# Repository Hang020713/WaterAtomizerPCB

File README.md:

# WaterAtomizerPCB
 A PCB Design of water atomizer

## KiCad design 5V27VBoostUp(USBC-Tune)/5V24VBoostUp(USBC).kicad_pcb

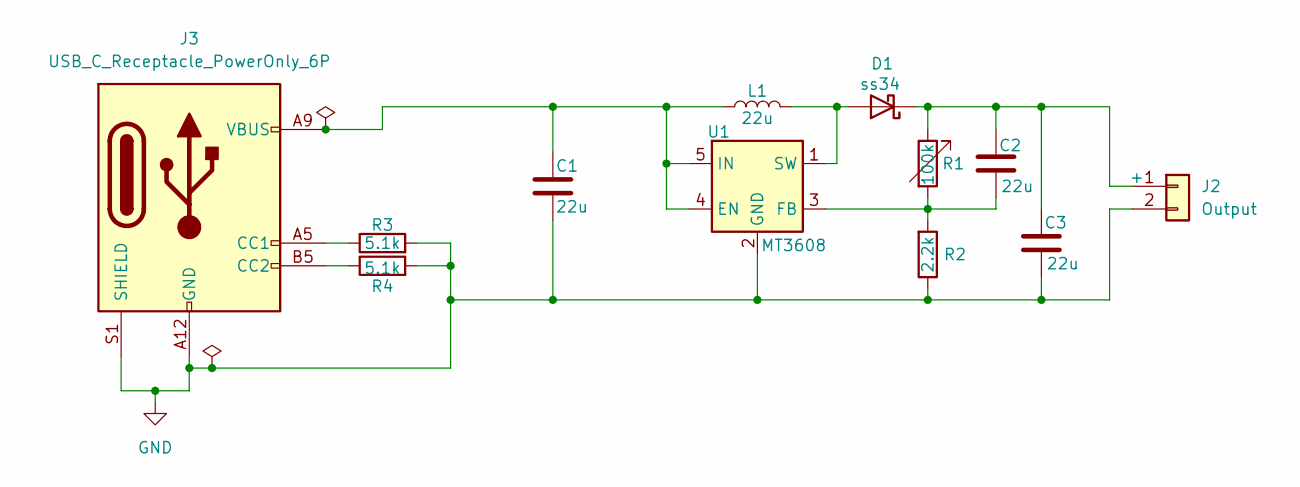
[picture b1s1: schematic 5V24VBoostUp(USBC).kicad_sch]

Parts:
C1, C2, C3: 22u; C_0603_1608Metric_Pad1.08x0.95mm_HandSolder
D1: ss34; D_SMA_Handsoldering
J2: Output; PinHeader_1x02_P2.00mm_Vertical
J3: USB_C_Receptacle_PowerOnly_6P; USB_C_Receptacle_HRO_TYPE-C-31-M-17
L1: 22u; L_0603_1608Metric_Pad1.05x0.95mm_HandSolder
R1: 100k; Potentiometer_Bourns_3296W_Vertical
R2: 2.2k; R_0603_1608Metric_Pad0.98x0.95mm_HandSolder
R3, R4: 5.1k; R_0603_1608Metric_Pad0.98x0.95mm_HandSolder
U1: MT3608; SOT-23-6_Handsoldering

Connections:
GND: C1.2, C3.2, J2.2, J3.A12 (GND), J3.B12 (GND), J3.S1 (SHIELD), R2.1, R3.2, R4.2, U1.2 (GND)
unnamed: D1.2 (A), L1.2, U1.1 (SW)
unnamed: C2.1, C3.1, D1.1 (K), J2.1, R1.1
unnamed: J3.A5 (CC1), R3.1
unnamed: J3.B5 (CC2), R4.1
unnamed: C1.1, J3.A9 (VBUS), J3.B9 (VBUS), L1.1, U1.4 (EN), U1.5 (IN)
unnamed: C2.2, R1.2, R2.2, U1.3 (FB)

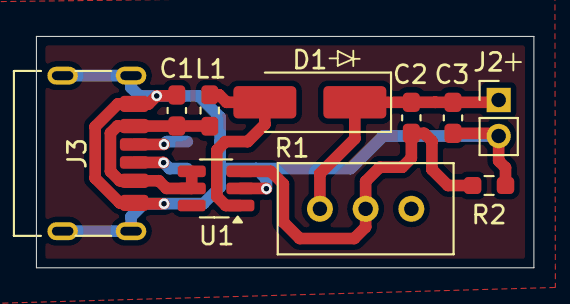
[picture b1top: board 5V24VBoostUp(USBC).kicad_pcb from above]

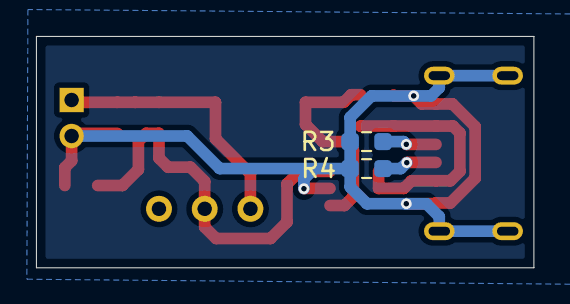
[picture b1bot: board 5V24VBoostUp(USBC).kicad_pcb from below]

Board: 2 copper layers, 27.6 x 12.9 mm, 12 parts (2 on the bottom side), 7 nets.

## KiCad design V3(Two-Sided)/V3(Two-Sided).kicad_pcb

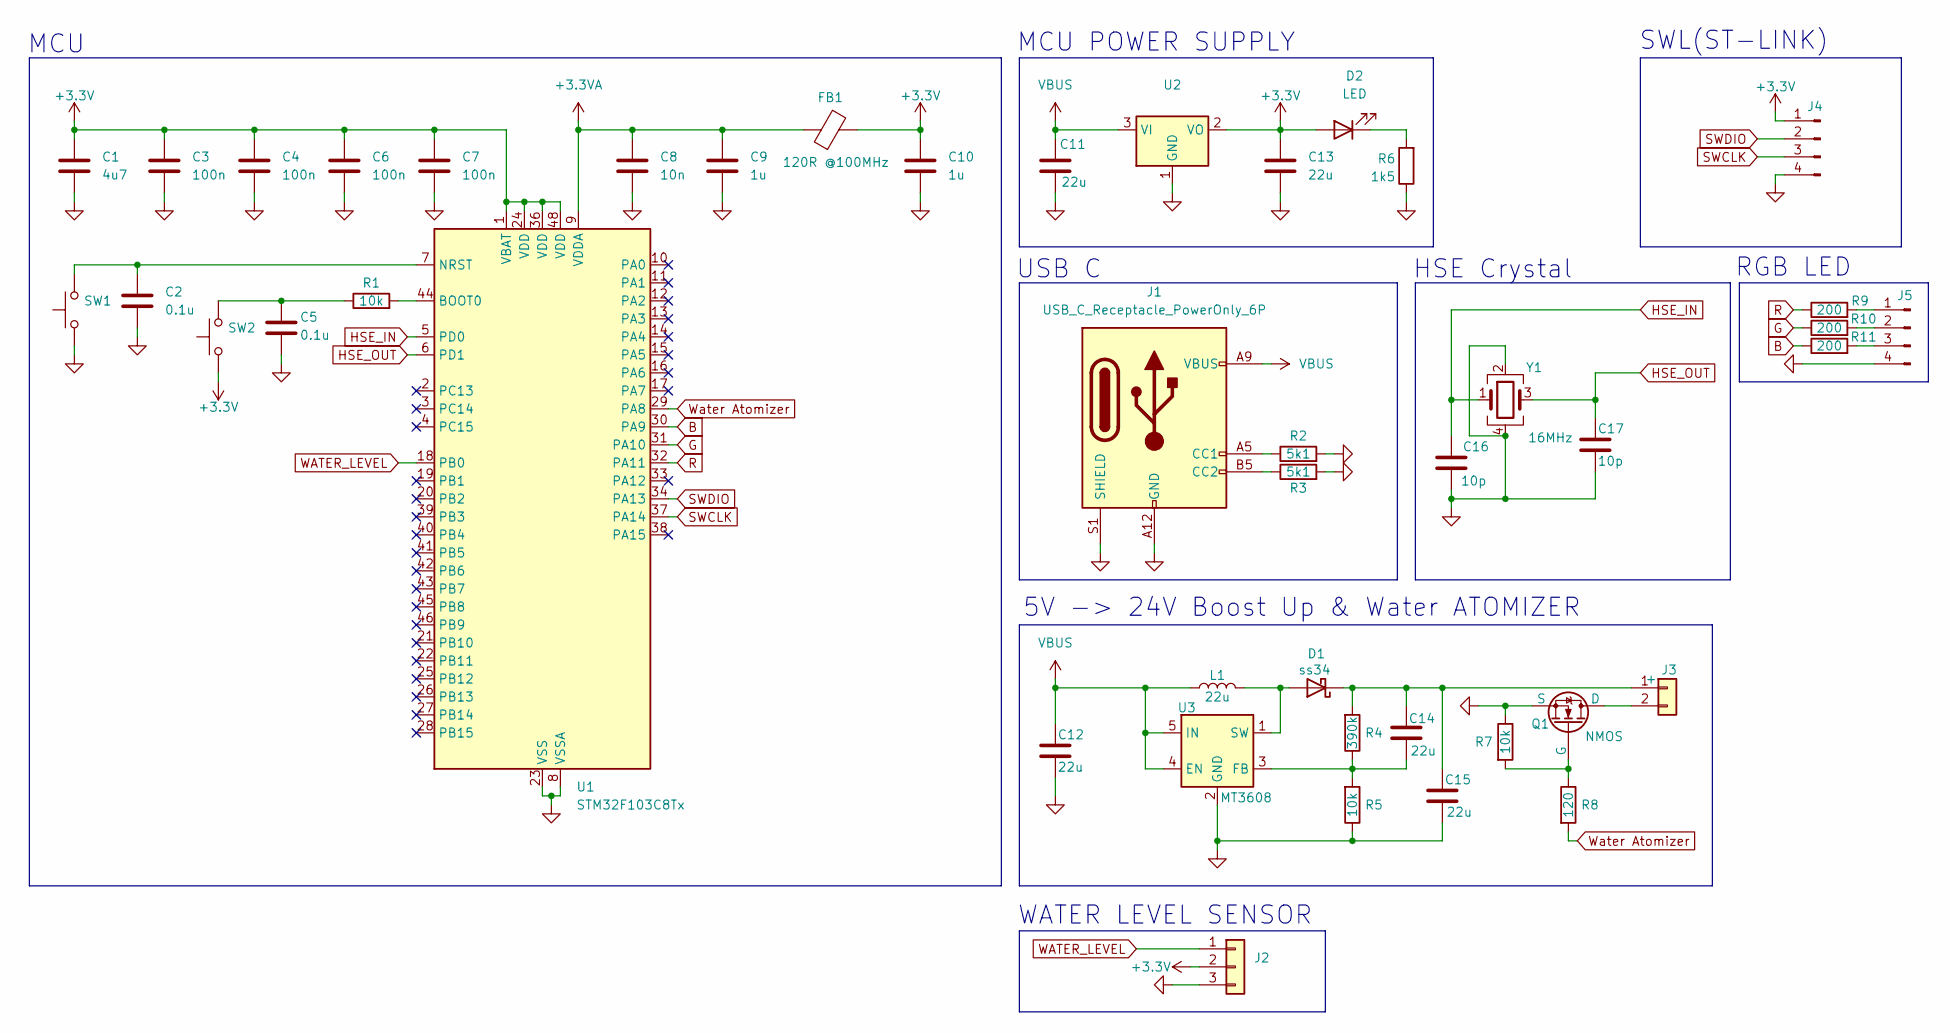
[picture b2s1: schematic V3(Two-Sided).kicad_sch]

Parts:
C1: 4u7; C_0603_1608Metric_Pad1.08x0.95mm_HandSolder
C2, C5: 0.1u; C_0603_1608Metric_Pad1.08x0.95mm_HandSolder
C3, C4, C6, C7: 100n; C_0603_1608Metric_Pad1.08x0.95mm_HandSolder
C8: 10n; C_0603_1608Metric_Pad1.08x0.95mm_HandSolder
C9, C10: 1u; C_0603_1608Metric_Pad1.08x0.95mm_HandSolder
C11, C12, C13, C14, C15: 22u; C_0603_1608Metric_Pad1.08x0.95mm_HandSolder
C16, C17: 10p; C_0603_1608Metric_Pad1.08x0.95mm_HandSolder
D1: ss34; D_SMA_Handsoldering
D2: LED; LED_0603_1608Metric_Pad1.05x0.95mm_HandSolder
FB1: 120R @100MHz; L_0603_1608Metric_Pad1.05x0.95mm_HandSolder
J1: USB_C_Receptacle_PowerOnly_6P; USB_C_Receptacle_HRO_TYPE-C-31-M-17
J2: WaterLevel; FanPinHeader_1x03_P2.54mm_Vertical
J3: Water Atomizer; PinHeader_1x02_P1.27mm_Vertical
J4: SWL; PinHeader_1x04_P2.54mm_Vertical
J5: RGB; PinHeader_1x04_P2.54mm_Vertical
L1: 22u; L_0603_1608Metric_Pad1.05x0.95mm_HandSolder
Q1: NMOS; SOT-23
R1, R5, R7: 10k; R_0603_1608Metric_Pad0.98x0.95mm_HandSolder
R2, R3: 5k1; R_0603_1608Metric_Pad0.98x0.95mm_HandSolder
R4: 390k; R_0603_1608Metric_Pad0.98x0.95mm_HandSolder
R6: 1k5; R_0603_1608Metric_Pad0.98x0.95mm_HandSolder
R8: 120; R_0603_1608Metric_Pad0.98x0.95mm_HandSolder
R9, R10, R11: 200; R_0603_1608Metric_Pad0.98x0.95mm_HandSolder
SW1, SW2: SW_Push; SW_PUSH_6mm
U1: STM32F103C8Tx; LQFP-48_7x7mm_P0.5mm
U2: LD1117S33TR_SOT223; SOT-223-3_TabPin2
U3: MT3608; SOT-23-6_Handsoldering
Y1: 16MHz; Crystal_SMD_3225-4Pin_3.2x2.5mm

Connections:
+3.3V: C1.1, C3.1, C4.1, C6.1, C7.1, C10.1, C13.1, D2.2 (A), FB1.2, J2.2, J4.1, SW2.1, U1.1 (VBAT), U1.24 (VDD), U1.36 (VDD), U1.48 (VDD), U2.2 (VO)
+3.3VA: C8.1, C9.1, FB1.1, U1.9 (VDDA)
B: R11.1, U1.30 (PA9)
G: R10.1, U1.31 (PA10)
GND: C1.2, C2.2, C3.2, C4.2, C5.2, C6.2, C7.2, C8.2, C9.2, C10.2, C11.2, C12.2, C13.2, C15.2, C16.2, C17.2, J1.A12 (GND), J1.B12 (GND), J1.S1 (SHIELD), J2.3, J4.4, J5.4, Q1.3 (S), R2.2, R3.2, R5.1, R6.1, R7.1, SW1.1, U1.8 (VSSA), U1.23 (VSS), U1.35 (VSS), U1.47 (VSS), U2.1 (GND), U3.2 (GND), Y1.2, Y1.4
HSE_IN: C16.1, U1.5 (PD0), Y1.1
HSE_OUT: C17.1, U1.6 (PD1), Y1.3
unnamed: C5.1, R1.1, SW2.2
unnamed: D1.2 (A), L1.2, U3.1 (SW)
unnamed: C14.1, C15.1, D1.1 (K), J3.1, R4.2
unnamed: D2.1 (K), R6.2
unnamed: J1.A5 (CC1), R2.1
unnamed: J1.B5 (CC2), R3.1
unnamed: J3.2, Q1.1 (D)
unnamed: J5.1, R9.2
unnamed: J5.2, R10.2
unnamed: J5.3, R11.2
unnamed: Q1.2 (G), R7.2, R8.1
unnamed: R1.2, U1.44 (BOOT0)
unnamed: C2.1, SW1.2, U1.7 (NRST)
unnamed: C14.2, R4.1, R5.2, U3.3 (FB)
R: R9.1, U1.32 (PA11)
SWCLK: J4.3, U1.37 (PA14)
SWDIO: J4.2, U1.34 (PA13)
VBUS: C11.1, C12.1, J1.A9 (VBUS), J1.B9 (VBUS), L1.1, U2.3 (VI), U3.4 (EN), U3.5 (IN)
WATER_LEVEL: J2.1, U1.18 (PB0)
Water Atomizer: R8.2, U1.29 (PA8)

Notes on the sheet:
RGB LED
WATER LEVEL SENSOR
5V -> 24V Boost Up & Water ATOMIZER
USB C
MCU
HSE Crystal
MCU POWER SUPPLY
SWL(ST-LINK)

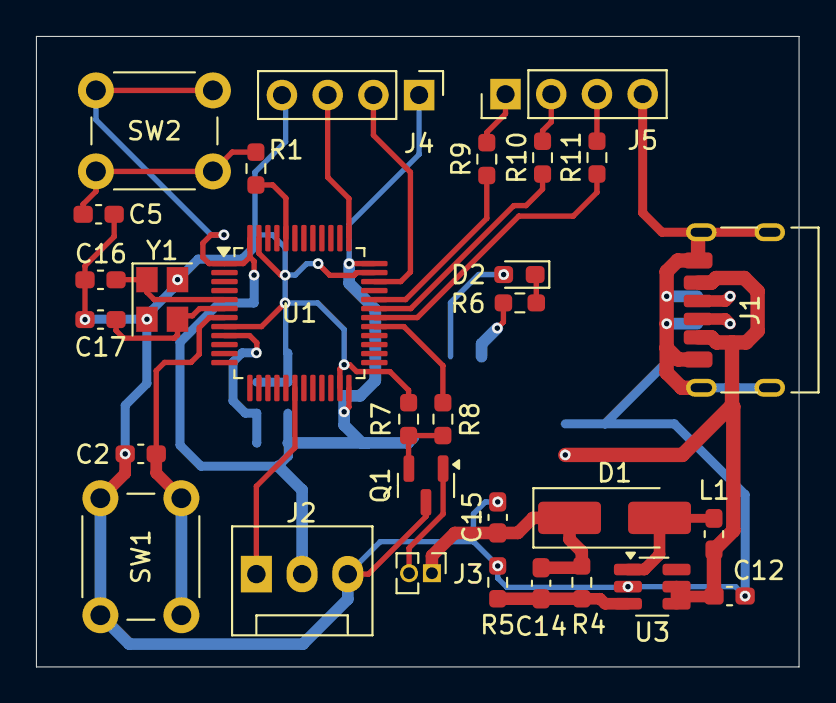
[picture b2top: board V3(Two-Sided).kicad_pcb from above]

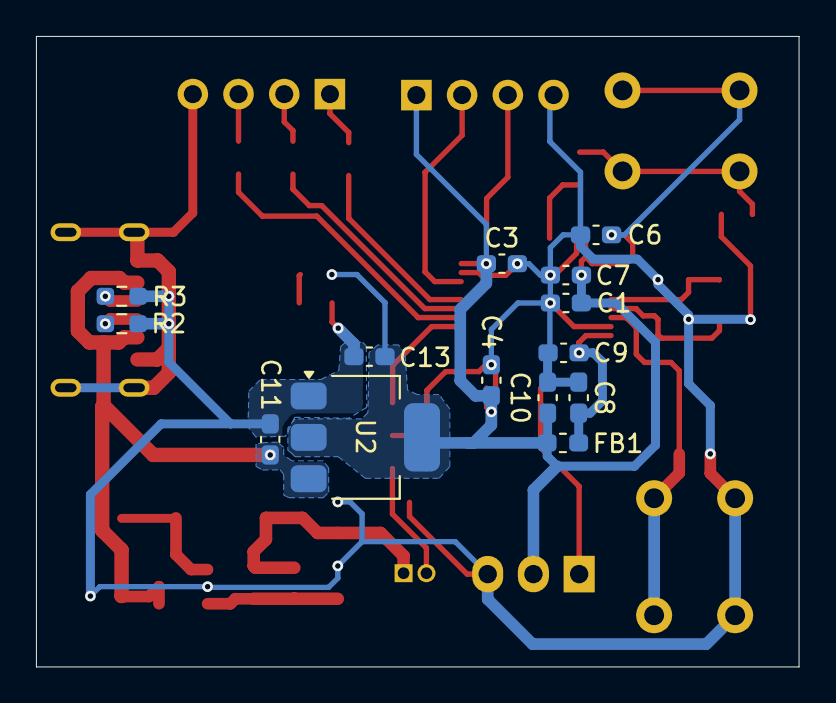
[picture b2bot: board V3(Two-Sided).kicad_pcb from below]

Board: 2 copper layers, 42.4 x 35.0 mm, 44 parts (14 on the bottom side), 27 nets.

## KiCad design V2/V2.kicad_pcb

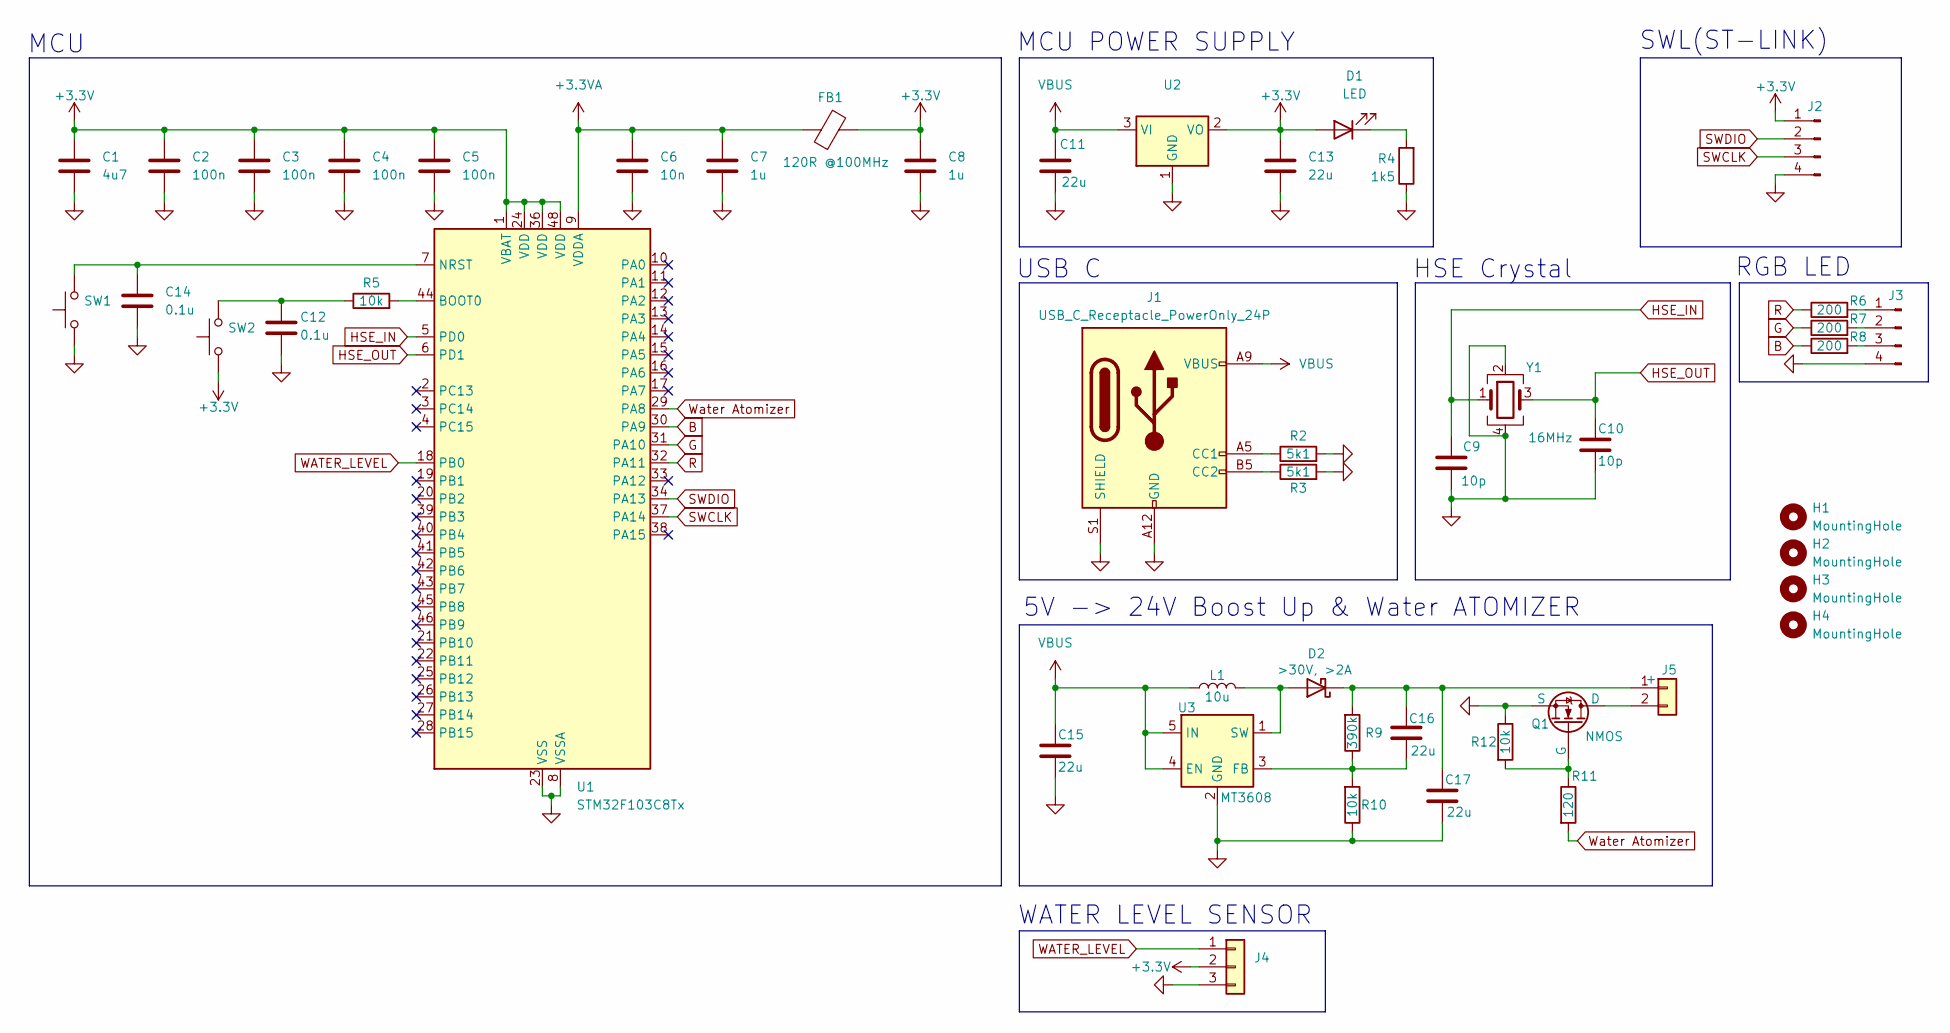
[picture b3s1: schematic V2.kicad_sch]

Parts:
C1: 4u7; C_0603_1608Metric_Pad1.08x0.95mm_HandSolder
C2, C3, C4, C5: 100n; C_0603_1608Metric_Pad1.08x0.95mm_HandSolder
C6: 10n; C_0603_1608Metric_Pad1.08x0.95mm_HandSolder
C7, C8: 1u; C_0603_1608Metric_Pad1.08x0.95mm_HandSolder
C9, C10: 10p; C_0603_1608Metric_Pad1.08x0.95mm_HandSolder
C11, C13, C15, C16, C17: 22u; C_0603_1608Metric_Pad1.08x0.95mm_HandSolder
C12, C14: 0.1u; C_0603_1608Metric_Pad1.08x0.95mm_HandSolder
D1: LED; LED_0603_1608Metric_Pad1.05x0.95mm_HandSolder
D2: >30V, >2A; D_SMA_Handsoldering
FB1: 120R @100MHz; L_0603_1608Metric_Pad1.05x0.95mm_HandSolder
H1, H2, H3, H4: MountingHole; MountingHole_2.1mm
J1: USB_C_Receptacle_PowerOnly_24P; USB_C_Receptacle_Amphenol_124019772112A
J2: SWL; PinHeader_1x04_P2.54mm_Vertical
J3: RGB; PinHeader_1x04_P2.54mm_Vertical
J4: WaterLevel; FanPinHeader_1x03_P2.54mm_Vertical
J5: Water Atomizer; PinHeader_1x02_P1.27mm_Vertical
L1: 10u; L_0603_1608Metric_Pad1.05x0.95mm_HandSolder
Q1: NMOS; SOT-23
R2, R3: 5k1; R_0603_1608Metric_Pad0.98x0.95mm_HandSolder
R4: 1k5; R_0603_1608Metric_Pad0.98x0.95mm_HandSolder
R5, R10, R12: 10k; R_0603_1608Metric_Pad0.98x0.95mm_HandSolder
R6, R7, R8: 200; R_0603_1608Metric_Pad0.98x0.95mm_HandSolder
R9: 390k; R_0603_1608Metric_Pad0.98x0.95mm_HandSolder
R11: 120; R_0603_1608Metric_Pad0.98x0.95mm_HandSolder
SW1, SW2: SW_Push; SW_PUSH_6mm
U1: STM32F103C8Tx; LQFP-48_7x7mm_P0.5mm
U2: LD1117S33TR_SOT223; SOT-223-3_TabPin2
U3: MT3608; SOT-23-6_Handsoldering
Y1: 16MHz; Crystal_SMD_3225-4Pin_3.2x2.5mm

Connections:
+3.3V: C1.1, C2.1, C3.1, C4.1, C5.1, C8.1, C13.1, D1.2 (A), FB1.2, J2.1, J4.2, SW2.1, U1.1 (VBAT), U1.24 (VDD), U1.36 (VDD), U1.48 (VDD), U2.2 (VO)
+3.3VA: C6.1, C7.1, FB1.1, U1.9 (VDDA)
B: R8.1, U1.30 (PA9)
G: R7.1, U1.31 (PA10)
GND: C1.2, C2.2, C3.2, C4.2, C5.2, C6.2, C7.2, C8.2, C9.2, C10.2, C11.2, C12.2, C13.2, C14.2, C15.2, C17.2, J1.A1 (GND), J1.A12 (GND), J1.B1 (GND), J1.B12 (GND), J1.S1 (SHIELD), J2.4, J3.4, J4.3, Q1.3 (S), R2.2, R3.2, R4.1, R10.1, R12.1, SW1.1, U1.8 (VSSA), U1.23 (VSS), U1.35 (VSS), U1.47 (VSS), U2.1 (GND), U3.2 (GND), Y1.2, Y1.4
HSE_IN: C9.1, U1.5 (PD0), Y1.1
HSE_OUT: C10.1, U1.6 (PD1), Y1.3
unnamed: C12.1, R5.1, SW2.2
unnamed: D1.1 (K), R4.2
unnamed: D2.2 (A), L1.2, U3.1 (SW)
unnamed: C16.1, C17.1, D2.1 (K), J5.1, R9.2
unnamed: J1.A5 (CC1), R2.1
unnamed: J1.B5 (CC2), R3.1
unnamed: J3.1, R6.2
unnamed: J3.2, R7.2
unnamed: J3.3, R8.2
unnamed: J5.2, Q1.1 (D)
unnamed: Q1.2 (G), R11.1, R12.2
unnamed: R5.2, U1.44 (BOOT0)
unnamed: C14.1, SW1.2, U1.7 (NRST)
unnamed: C16.2, R9.1, R10.2, U3.3 (FB)
R: R6.1, U1.32 (PA11)
SWCLK: J2.3, U1.37 (PA14)
SWDIO: J2.2, U1.34 (PA13)
VBUS: C11.1, C15.1, J1.A4 (VBUS), J1.A9 (VBUS), J1.B4 (VBUS), J1.B9 (VBUS), L1.1, U2.3 (VI), U3.4 (EN), U3.5 (IN)
WATER_LEVEL: J4.1, U1.18 (PB0)
Water Atomizer: R11.2, U1.29 (PA8)

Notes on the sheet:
MCU POWER SUPPLY
HSE Crystal
USB C
5V -> 24V Boost Up & Water ATOMIZER
MCU
RGB LED
WATER LEVEL SENSOR
SWL(ST-LINK)

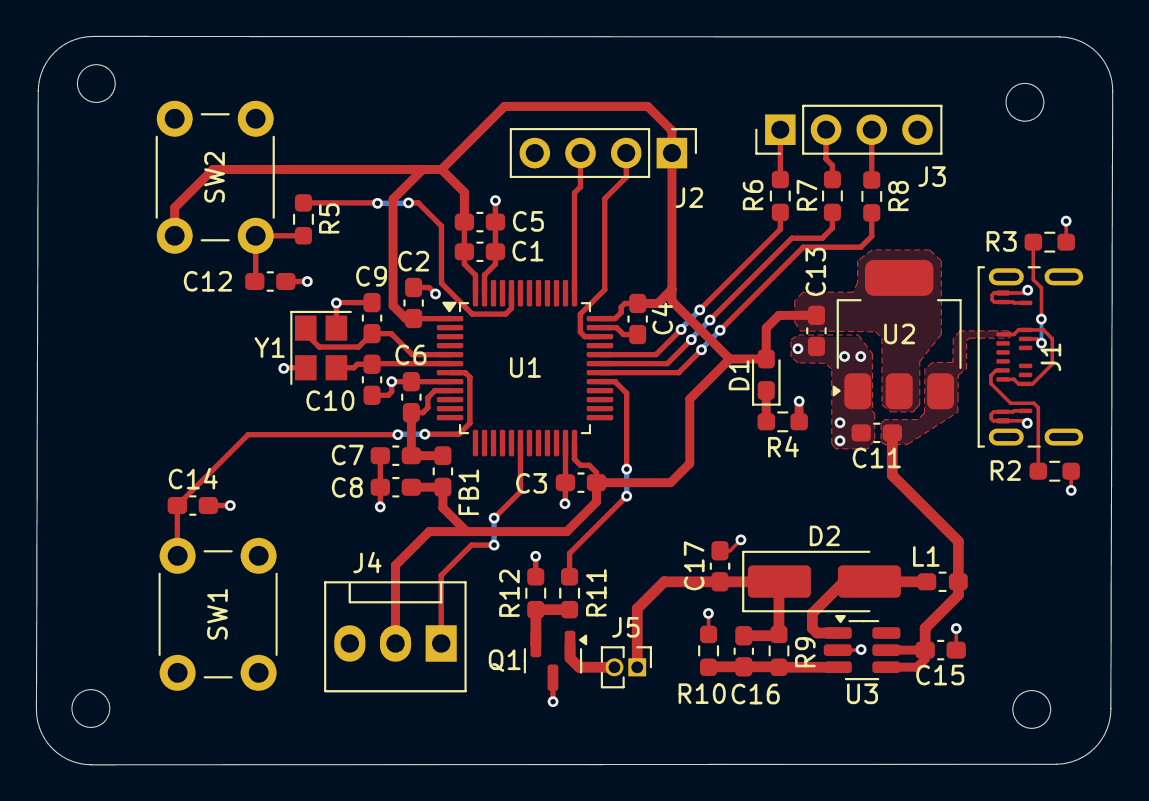
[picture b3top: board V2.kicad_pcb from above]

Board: 2 copper layers, 59.8 x 40.5 mm, 48 parts (0 on the bottom side), 27 nets.

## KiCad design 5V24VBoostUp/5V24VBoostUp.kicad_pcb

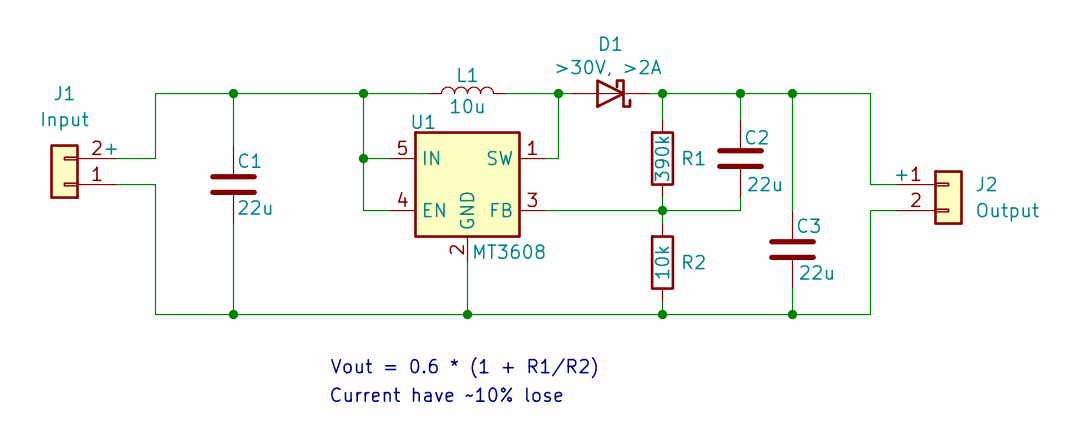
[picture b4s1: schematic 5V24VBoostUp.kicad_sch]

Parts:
C1, C2, C3: 22u; C_0603_1608Metric_Pad1.08x0.95mm_HandSolder
D1: >30V, >2A; D_SMA_Handsoldering
J1: Input; PinHeader_1x02_P2.00mm_Vertical
J2: Output; PinHeader_1x02_P2.00mm_Vertical
L1: 10u; L_0603_1608Metric_Pad1.05x0.95mm_HandSolder
R1: 390k; R_0603_1608Metric_Pad0.98x0.95mm_HandSolder
R2: 10k; R_0603_1608Metric_Pad0.98x0.95mm_HandSolder
U1: MT3608; SOT-23-6_Handsoldering

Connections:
unnamed: D1.2 (A), L1.2, U1.1 (SW)
unnamed: C2.1, C3.1, D1.1 (K), J2.1, R1.2
unnamed: C1.2, C3.2, J1.1, J2.2, R2.1, U1.2 (GND)
unnamed: C1.1, J1.2, L1.1, U1.4 (EN), U1.5 (IN)
unnamed: C2.2, R1.1, R2.2, U1.3 (FB)

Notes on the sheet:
Current have ~10% lose
Vout = 0.6 * (1 + R1/R2)

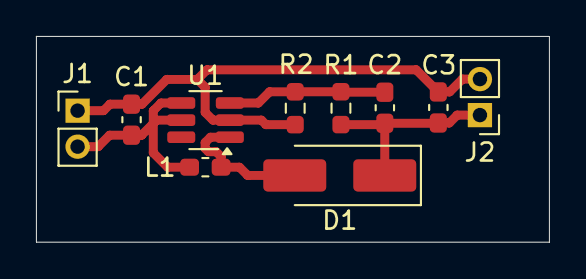
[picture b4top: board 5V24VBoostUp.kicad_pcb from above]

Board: 2 copper layers, 28.5 x 11.4 mm, 10 parts (0 on the bottom side), 5 nets.

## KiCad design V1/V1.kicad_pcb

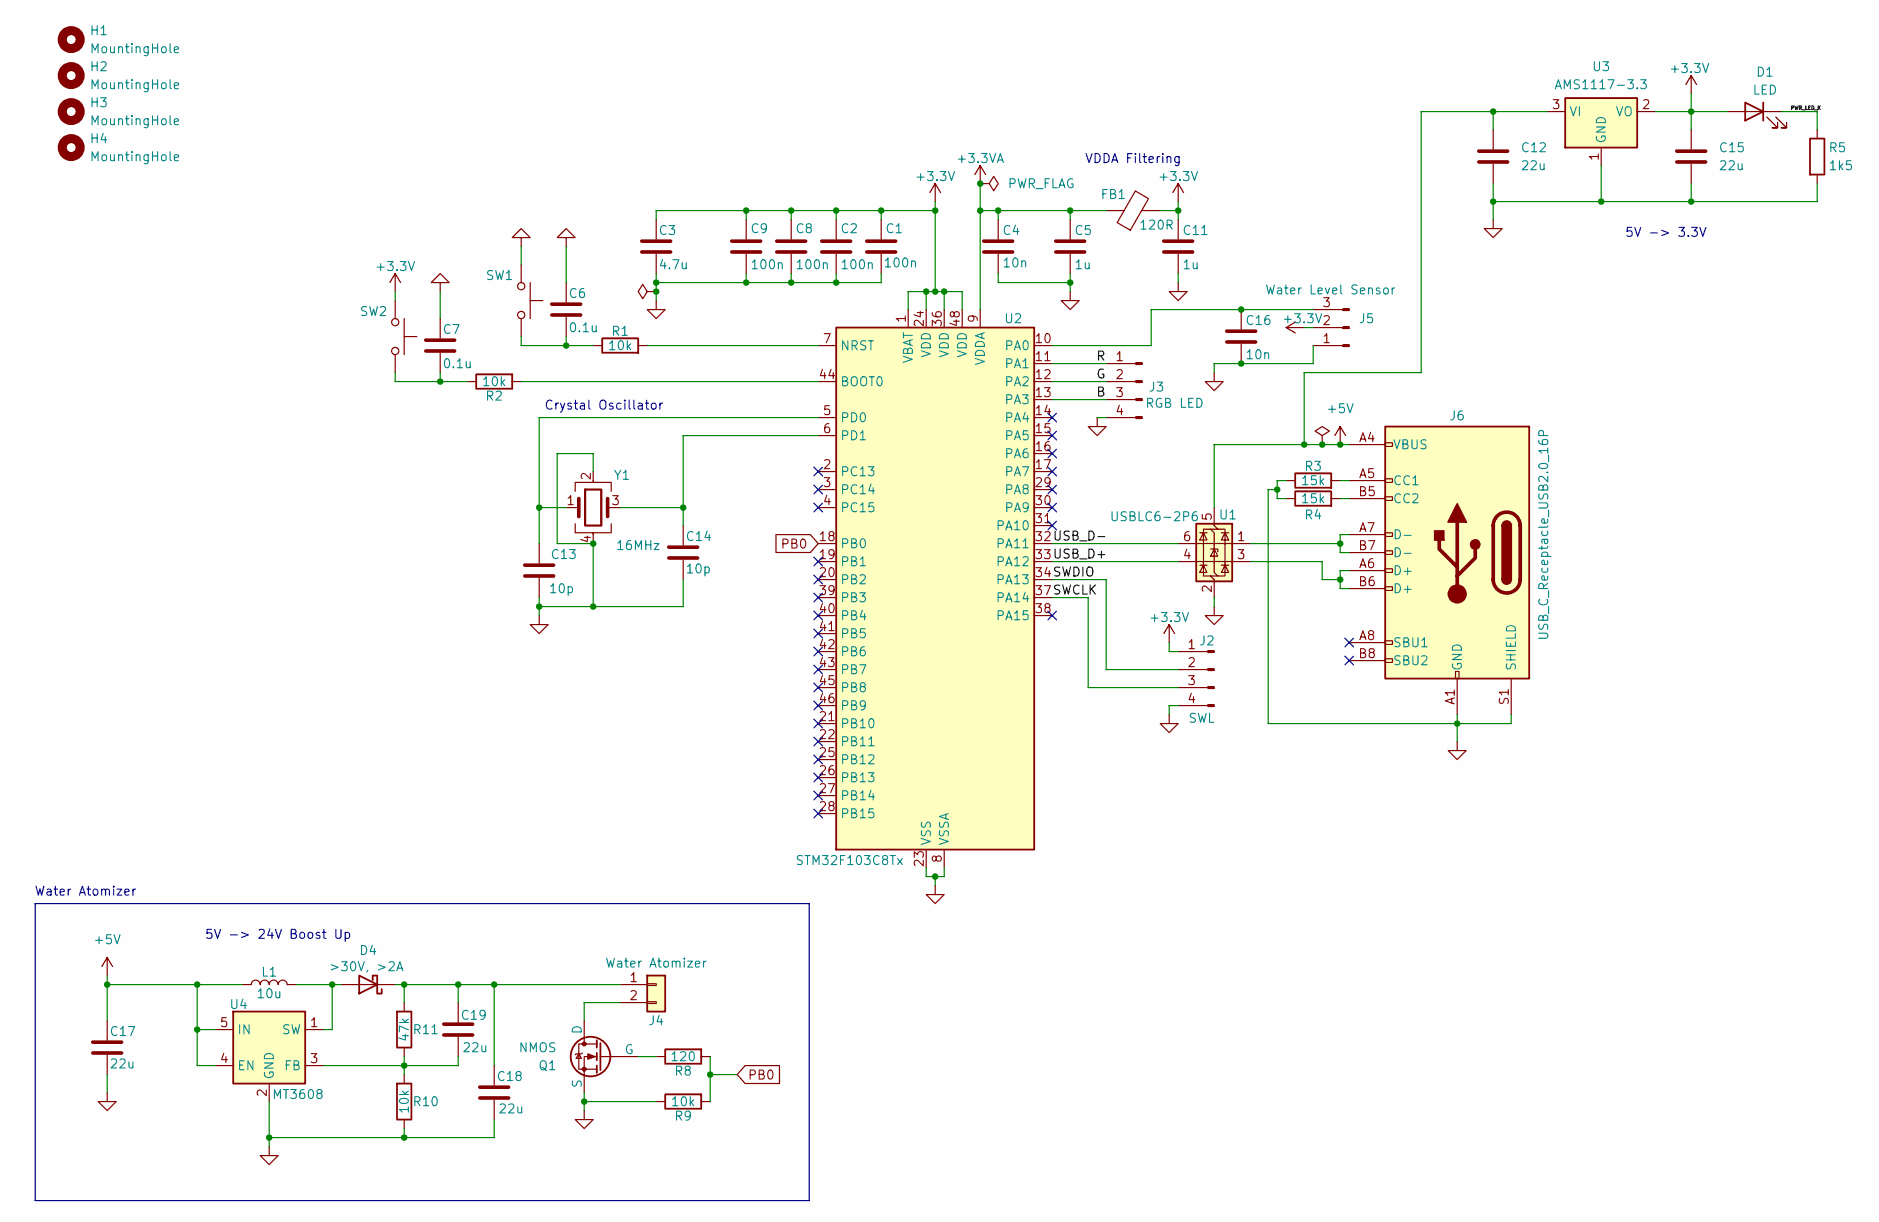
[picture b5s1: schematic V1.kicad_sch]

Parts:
C1, C2, C8, C9: 100n; C_0805_2012Metric_Pad1.18x1.45mm_HandSolder
C3: 4.7u; C_0805_2012Metric_Pad1.18x1.45mm_HandSolder
C4, C16: 10n; C_0805_2012Metric_Pad1.18x1.45mm_HandSolder
C5, C11: 1u; C_0805_2012Metric_Pad1.18x1.45mm_HandSolder
C6, C7: 0.1u; C_0805_2012Metric_Pad1.18x1.45mm_HandSolder
C12, C15, C17, C18, C19: 22u; C_0805_2012Metric_Pad1.18x1.45mm_HandSolder
C13, C14: 10p; C_0805_2012Metric_Pad1.18x1.45mm_HandSolder
D1: LED; LED_0805_2012Metric
D4: >30V, >2A; D_SMA_Handsoldering
FB1: 120R; L_0603_1608Metric_Pad1.05x0.95mm_HandSolder
H1, H2, H3, H4: MountingHole; MountingHole_2.1mm
J2: SWL; PinHeader_1x04_P2.54mm_Vertical
J3: RGB LED; PinHeader_1x04_P1.27mm_Vertical
J4: Water Atomizer; PinHeader_1x02_P1.27mm_Vertical
J5: Water Level Sensor; FanPinHeader_1x03_P2.54mm_Vertical
J6: USB_C_Receptacle_USB2.0_16P; USB_C_Receptacle_HRO_TYPE-C-31-M-12
L1: 10u; L_0402_1005Metric_Pad0.77x0.64mm_HandSolder
Q1: NMOS; TO-220F-3_Vertical
R1, R2, R9, R10: 10k; R_0603_1608Metric_Pad0.98x0.95mm_HandSolder
R3, R4: 15k; R_0603_1608Metric_Pad0.98x0.95mm_HandSolder
R5: 1k5; R_0603_1608Metric_Pad0.98x0.95mm_HandSolder
R8: 120; R_0603_1608Metric_Pad0.98x0.95mm_HandSolder
R11: 47k; R_0603_1608Metric_Pad0.98x0.95mm_HandSolder
SW1, SW2: SW_Push; SW_PUSH_6mm
U1: USBLC6-2P6; SOT-666
U2: STM32F103C8Tx; LQFP-48_7x7mm_P0.5mm
U3: AMS1117-3.3; SOT-223-3_TabPin2
U4: MT3608; SOT-23-6_Handsoldering
Y1: 16MHz; Crystal_SMD_3225-4Pin_3.2x2.5mm

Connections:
+3.3V: C1.1, C2.1, C3.1, C8.1, C9.1, C11.1, C15.1, D1.2 (A), FB1.2, J2.1, J5.2, SW2.2, U2.1 (VBAT), U2.24 (VDD), U2.36 (VDD), U2.48 (VDD), U3.2 (VO)
+3.3VA: C4.1, C5.1, FB1.1, U2.9 (VDDA)
+5V: C12.1, C17.1, J6.A4 (VBUS), J6.A9 (VBUS), J6.B4 (VBUS), J6.B9 (VBUS), L1.1, U1.5 (VBUS), U3.3 (VI), U4.4 (EN), U4.5 (IN)
/B: J3.3, U2.13 (PA3)
/G: J3.2, U2.12 (PA2)
/PWR_LED_K: D1.1 (K), R5.1
/R: J3.1, U2.11 (PA1)
/SWCLK: J2.3, U2.37 (PA14)
/SWDIO: J2.2, U2.34 (PA13)
/USB_D+: U1.4 (I/O2), U2.33 (PA12)
/USB_D-: U1.6 (I/O1), U2.32 (PA11)
GND: C1.2, C2.2, C3.2, C4.2, C5.2, C6.1, C7.1, C8.2, C9.2, C11.2, C12.2, C13.2, C14.2, C15.2, C16.2, C17.2, C18.2, J2.4, J3.4, J5.1, J6.A1 (GND), J6.A12 (GND), J6.B1 (GND), J6.B12 (GND), J6.S1 (SHIELD), Q1.3 (S), R3.1, R4.1, R5.2, R9.1, R10.1, SW1.2, U1.2 (GND), U2.8 (VSSA), U2.23 (VSS), U2.35 (VSS), U2.47 (VSS), U3.1 (GND), U4.2 (GND), Y1.2, Y1.4
unnamed: C6.2, R1.1, SW1.1
unnamed: C7.2, R2.1, SW2.1
unnamed: D4.2 (A), L1.2, U4.1 (SW)
unnamed: C18.1, C19.1, D4.1 (K), J4.1, R11.2
unnamed: J4.2, Q1.1 (D)
unnamed: C16.1, J5.3, U2.10 (PA0)
unnamed: J6.A5 (CC1), R3.2
unnamed: J6.B5 (CC2), R4.2
unnamed: J6.A6 (D+), J6.B6 (D+), U1.3 (I/O2)
unnamed: J6.A7 (D-), J6.B7 (D-), U1.1 (I/O1)
unnamed: Q1.2 (G), R8.1
unnamed: R2.2, U2.44 (BOOT0)
unnamed: R1.2, U2.7 (NRST)
unnamed: C13.1, U2.5 (PD0), Y1.1
unnamed: C14.1, U2.6 (PD1), Y1.3
unnamed: C19.2, R10.2, R11.1, U4.3 (FB)
PB0: R8.2, R9.2, U2.18 (PB0)

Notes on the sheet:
5V -> 3.3V
Water Atomizer
5V -> 24V Boost Up
Crystal Oscillator
VDDA Filtering

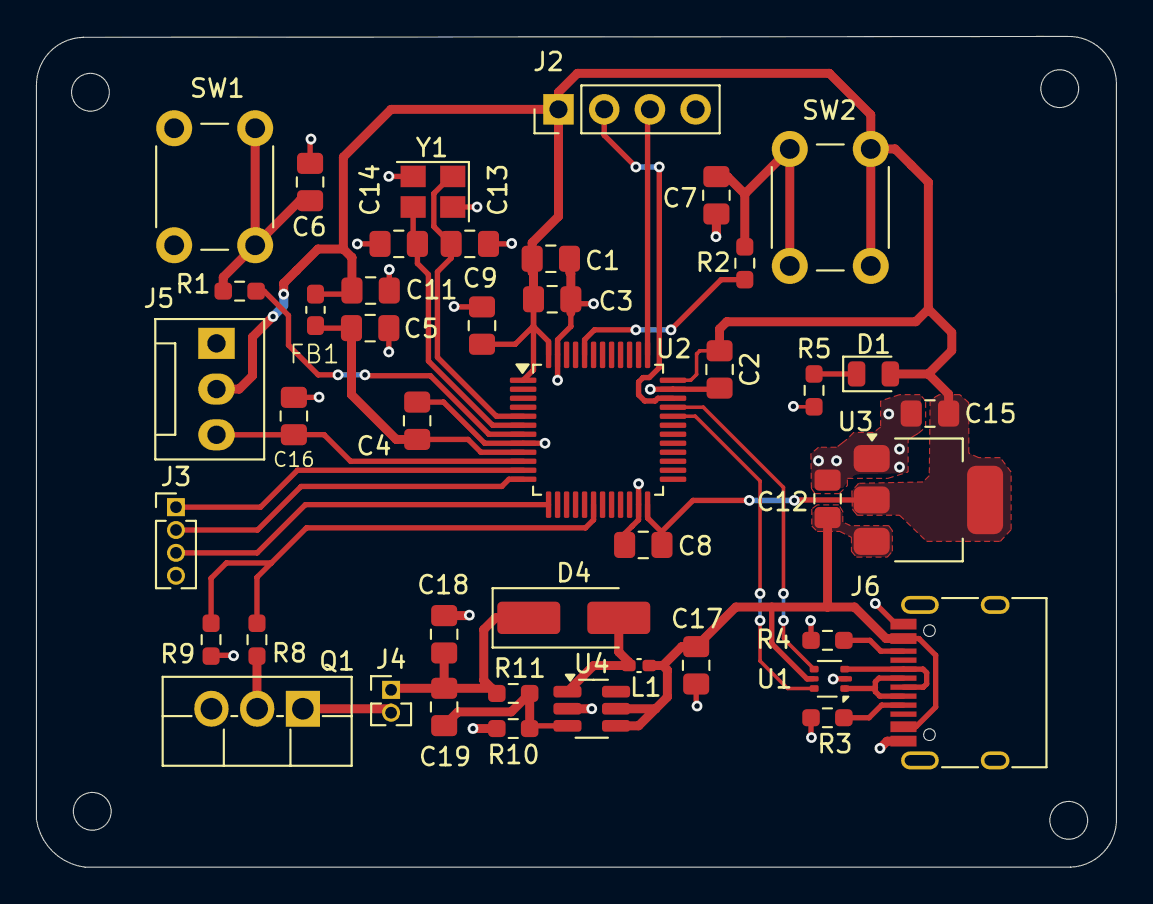
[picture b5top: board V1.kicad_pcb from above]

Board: 2 copper layers, 60.0 x 46.2 mm, 48 parts (0 on the bottom side), 29 nets.

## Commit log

2025-01-24 Update version 1&2&3
2025-03-22 Update V2
2025-03-23 Update Backup
